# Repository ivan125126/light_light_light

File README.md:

# Lux

A wireless LED performance prop system from the Department of Engineering Science, NCKU. As the props spin, they use **Persistence of Vision (POV)** to draw 2D images in the air, synchronized over Wi-Fi to music. They are mainly performed at freshman orientation camps.

> Full design write-up (electronics, mechanical, firmware, editor): [LightPOV project page](https://hsupingjhao.info/projects/LightPOV/)

## Devices

| Device | Photo | Description | Code |
|---|:---:|---|---|
| **Light Stick** |  | ESP32 + WS2812 LED strip in a transparent PC tube, powered by an 18650 Li-ion battery | [`LightPOV/`](LightPOV/) |
| **Light Snake** |  | Shares the Stick's ESP32 core board and firmware, swung on a rope | [`LightPOV/`](LightPOV/) |
| **Light Ball** |  | ESP-12F (ESP8266) + RGB LEDs in a semi-transparent PE container | [`LightBall/`](LightBall/) |

## 🎬 Performances

Click a thumbnail to watch on YouTube.

**117th Freshman Orientation Camp**

| Stick | Ball | Snake |
|:---:|:---:|:---:|
|  |  |  |

| 27th ESCamp (Stick, Ball, Snake) | 118th Freshman Orientation Camp (Stick) |
|:---:|:---:|
|  |  |

## Repository Layout

| Folder | Contents | Status |
|---|---|---|
| [`LightPOV/`](LightPOV/) | Stick & Snake: ESP32 firmware, effect editor (ControlPanel_v3), PCB and 3D models | Active development |
| [`LightBall/`](LightBall/) | Ball: ESP8266 firmware, controller, C# helper tool, PCB | Maintained |

`LightPOV/legacy/` holds previous control panels and past performance files. It is kept for reference only, so please don't develop in it.

## Usage

### Requirements

- [Node.js](https://nodejs.org/) 20+
- [Arduino IDE](https://www.arduino.cc/en/software) with the ESP32 board package and the `FastLED`, `cppQueue` and `MPU6050` libraries

### 1. Effect editor (ControlPanel_v3)

```bash
cd LightPOV/ControlPanel_v3
npm install
npm run dev        # open http://localhost:3000
npm run test       # run unit tests
```

### 2. Hardware server

The props fetch effects and sync time from the server over Wi-Fi. Each server serves a different prop:

| Server | How to start | Port | Prop |
|---|---|---|---|
| `ControlPanel_v3/server/server.ts` | `cd LightPOV/ControlPanel_v3/server && npm install && npm run start` | 10240 | TBD |
| `ControlPanel_v3/src/server/server.js` | `cd LightPOV/ControlPanel_v3/src/server && npm install && node server.js` (on Windows, run `啟動server.bat`) | 20480 | TBD |

### 3. Flashing the firmware (LightPOV)

1. Open `LightPOV/ESP32/ESP32.ino` in Arduino IDE
2. Set the Wi-Fi SSID/password and `LUX_ID_DEFAULT` (each prop's ID) in `config.h`
3. Select the ESP32 board and upload; later updates can be pushed over Wi-Fi (OTA)

### 4. Performance workflow

TBD (edit effects → push to server → props connect → play music to start)

### LightBall

```bash
cd LightBall/controller
npm install
node server.js     # open http://localhost:3000
```

The firmware is in `LightBall/Code/LightBall_v2/`.

### Developer docs

- [ControlPanel_v3 developer quick start](LightPOV/ControlPanel_v3/docs/README.md) (Chinese)
- [Architecture](LightPOV/ControlPanel_v3/docs/architecture.md)
- [Hardware protocol](LightPOV/ControlPanel_v3/docs/hardware-protocol.md)

For questions, please open an [Issue](https://github.com/ivan125126/light_light_light/issues).

## What's Next

**Hardware**
- [ ] Bring up the [core PCB v2.0](LightPOV/hardware/PCB/core_pcb/) (chip-down ESP32, 14500 battery, JST connectors) and verify it works end to end
- [ ] Measure whether the LED strip draws more than 2 A from the independent power supply
- [ ] Magnetic charging with a 3D-printed enclosure
- [ ] Next-generation device: replace modules with mounted electronics to shrink the core radius

**Software**
- [ ] Document the end-to-end performance workflow (the TBD items above)

## Acknowledgements

This project is forked from [sciyen/ES-Lux](https://github.com/sciyen/ES-Lux) (NCKU ES Makers Program). Thanks to the original authors [@sciyen](https://github.com/sciyen) and [@BensonYang1999](https://github.com/BensonYang1999). The Lux-starter kit from the original project is not included in this repo; see the upstream repo if you need it.

Licensed under the [BSD 3-Clause License](LICENSE).

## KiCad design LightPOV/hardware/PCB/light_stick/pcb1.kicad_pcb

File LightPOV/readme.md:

# Light POV (光蛇)

## Important Features
- Using `Effects` to manage the displaying time of an effect.
- Using `ColorScheduler` to set colors with pre-defined functions.
- Using OTA to upload program through Wifi.
- Using a web server to send commands to POVs for synchronization.
- Displaying pre-loaded bitmaps to display complex patterns.

## Project file structure
```
├── ControlPanel_v3             : Effect editor (Vite + Vue 3 + TypeScript), see ControlPanel_v3/docs/
│   ├── src                     : Web front-end
│   ├── src/server/server.js    : Hardware server (port 20480)
│   ├── server/server.ts        : Hardware server (port 10240)
│   └── docs                    : Developer docs (architecture, hardware protocol)
├── ESP32                       : Program for ESP32
│   ├── ESP32.ino               : Main program code
│   ├── ConfigManager.cpp/.h    : Persistent (ROM) configuration
│   ├── acc.cpp/.h              : Accelerometer module
│   ├── bitmaps.h               : bitmaps for displaying patterns
│   ├── communication.cpp/.h    : Wifi connection and OTA
│   ├── config.h                : Configuration for Wifi password, host address, etc.
│   ├── core.h                  : Definitions of pattern functions
│   └── modes.cpp/.h            : Implementations of patterns, the scheduling of effects
├── hardware
│   ├── *.SLDPRT / *.STL        : SolidWorks parts and printable meshes
│   └── PCB
│       ├── core_pcb            : ESP32 core board v2.0
│       ├── light_stick         : KiCad project for the stick
│       └── easyeda_projects.7z : Earlier EasyEDA projects (stick, ball, hand light)
├── legacy                      : Previous control panels and performance files (read-only)
├── readme.md
└── test                        : Some module test code
```

## The hardware 
The schematic is an unrecorded artifact. The hardware is a simple design with an ESP32, a WS2812 LED strip, and a 18650 battery. 
PCB designs are in `hardware/PCB/`.

## Welcome for Contribution
If you are interested in this project, feel free to contribute to this project.
If you have any questions, please open an issue or contact @sciyen via sciyen.ycc@gmail.com .

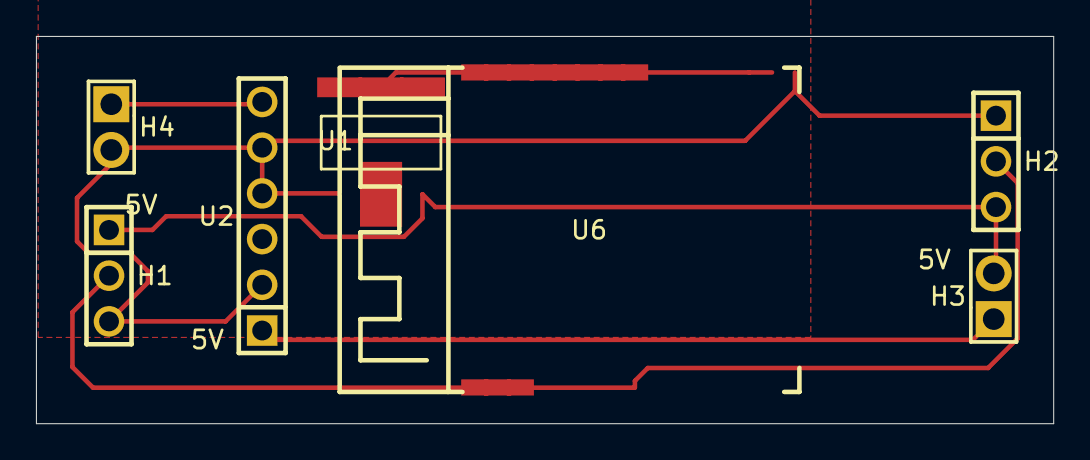
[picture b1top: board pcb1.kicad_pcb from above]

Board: 2 copper layers, 56.5 x 21.5 mm, 7 parts (0 on the bottom side), 6 nets.

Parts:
H1: H1; a7888812b2a44d4dbb4db40b5bdf1a47
H2: H2; a7888812b2a44d4dbb4db40b5bdf1a47
H3: H3; e6a0d22e109948b3b5ea7eec97f41443
H4: H4; e6a0d22e109948b3b5ea7eec97f41443
U1: U1; abe642fa63f74328b63ecdce04e13a56
U2: U2; 7f07cc57892d4498bd1535c8f47795ae
U6: U6; 9602c4eddce44f08a1cc8879e6cb76c3

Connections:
$1N2274: H4.2, U2.1
$1N2338: H3.2, U2.6
$1N2406: U1.4, U6.2, U6.3
$1N2432: H1.3, H2.1, H3.1, U1.3
$1N2449: H1.2, H2.2, U6.33
GND: H1.1, H2.3, H4.1, U1.1, U2.2, U2.3, U2.5, U6.1

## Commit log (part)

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2025-11-11 add new control system
2026-03-28 branch start
2026-03-29 add todo.md
2026-04-03 feat: add TypeScript type definitions
2026-04-03 feat: add effect constants and built-in definitions
2026-04-03 feat: add serializer service with hardware string encoding (TDD)
2026-04-03 fix: add thumbnail to EffectDefinition, correct startTime unit docs, note positionFix rename
2026-04-03 feat: add audioService and hardwareService
2026-04-03 feat: add Pinia stores (effect, timeline, audio, project)
2026-04-03 fix: add instanceToHardwareString test coverage, add normalizeTo255 JSDoc
2026-04-03 fix: stop playback before loading new audio, add error handling to setExecutionMode
2026-04-03 chore: Plan 1 complete — Foundation layer ready
2026-04-03 Revert "chore: Plan 1 complete — Foundation layer ready"
    This reverts commit aa8beef4974c5c2a19398693b041e713e15a12d3.
2026-04-03 chore: add .gitignore (exclude node_modules and dist)
2026-04-03 docs: add Plan 2 (UI Components) and Plan 3 (Preview/Server/Docs) implementation plans
2026-04-03 feat: add App layout and placeholder components
2026-04-03 feat: migrate EffectBlock to TypeScript, decouple from globals
2026-04-03 feat: implement AssetLibrary component
2026-04-03 feat: implement TimelinePanel and TrackCanvas with Fabric.js
2026-04-03 feat: implement ParameterPanel with HSV channels and extra params
2026-04-03 feat: implement PreviewPanel, fix auto-update bug
2026-04-03 feat: add toolbar with save/load/export/import project
2026-04-03 chore: remove legacy script.js and EffectBlock.js
2026-04-05 refactor: replace trackCount with tracks[] in timelineStore, add removeTrack/renameTrack
2026-04-05 fix: export Track interface, fix addTrack numbering after deletion
2026-04-05 style: add track-row, track-label, track-actions, track-delete CSS classes
2026-04-05 fix: cancelEdit flag prevents blur saving on Esc, snapshot toReindex before mutations
2026-04-05 feat: add selectionStore for multi-select and clipboard state
2026-04-05 feat: add undoStore with snapshot-based undo, add restoreInstances to effectStore
2026-04-05 test: tighten undoStore stack-cap assertion, add multi-step undo test
2026-04-05 feat: TimelinePanel — Backspace multi-delete, Cmd+X/C/V cut/copy/paste, Cmd+Z undo
2026-04-05 fix: keep multi-selection on drag, co-move all selected blocks
2026-04-05 fix: replace continue with return inside forEach callbacks
2026-04-05 fix: skip co-moving blocks in boundary calc, force renderAll after co-move
2026-04-05 fix: call setCoords after reposition so control handles follow blocks on pan/zoom
2026-04-07 feat: update LuxUnit type — add trackIndex, remove modeName; add luxUnits to ProjectFile
2026-04-07 feat: hardwareStore — remove modeName, add trackIndex + setTrackIndex action
2026-04-07 fix: PerformancePreview — deduplicate instanceToEffectData call, document broadcast behavior
2026-04-08 feat: useActiveEffect returns MODES_CLEAR for empty track time
2026-04-08 feat: tracksToEffectMap fills gaps with MODES_CLEAR
2026-04-08 feat: pass totalDuration to tracksToEffectMap in pushToServer
2026-04-08 fix: send CLEAR to preview when cursor is on empty track space
2026-04-09 feat(server): add /health endpoint
2026-04-09 feat(vite): proxy /health to server
2026-04-09 feat(service): add checkServerHealth + failing store tests
2026-04-09 feat(store): server online polling
2026-04-09 fix(tests): use flushPromises for store polling tests
    Replace vi.runAllTimersAsync() with flushPromises() from @vue/test-utils
    to flush the microtask queue after startServerPolling() without repeatedly
    firing the setInterval (which hit Vitest's 10000-timer safety limit).
2026-04-09 fix(store): await initial _checkServer in startServerPolling
2026-04-09 feat(ui): server status indicator in toolbar
2026-04-09 add push effect map proxy
2026-04-10 4/10陳柏宇到台南了
2026-04-10 feat(ui):configurate the preview panel
2026-04-10 feat(store): add uiStore with appMode toggle
2026-04-10 feat(store): add playbackRate to audioStore
2026-04-10 feat(audio): apply playbackRate in audioService
2026-04-10 refactor(server): remove dead /settime and /gettime routes
2026-04-10 fix(timeline): pass playbackRate to seekTo(), reset invalid speed input
2026-04-10 feat(hotkeys): Space play/pause, Ctrl+B split effect at cursor
2026-04-10 feat(params): editable start_time and duration in ParameterPanel
2026-04-10 fix(params): add CSS for timing inputs, reset invalid input values
2026-04-10 feat(ui): add Edit/Perform mode toggle switch in toolbar
2026-04-10 feat(perform): lock TrackCanvas drag and AssetLibrary drag in perform mode
2026-04-10 feat(perform): disable ParameterPanel in perform mode
2026-04-10 feat(perform): hide edit controls in TimelinePanel perform mode
2026-04-10 fix(timeline): re-anchor tick baseline on rate change, block Ctrl+B in perform mode, add speed control CSS
2026-04-16 4/16 fix some bug
2026-04-16 Refactor code structure for improved readability and maintainability
2026-05-06 map the track name
2026-05-06 Revert "chore: gitignore Legacy Control Panel — freeze as read-only archive"
    This reverts commit 905631b9baa2fe936f945ed86385300ac83dd2e8.
